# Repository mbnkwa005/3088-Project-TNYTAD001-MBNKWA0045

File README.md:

# EEE3088F Micro-Mouse Project

### Authors
- Tadiwa Tanyanyiwa
- Kwanele Mabanga

Welcome to the GitHub repository for our project!, which includes two key submodules: the Power submodule and the Sensing submodule.
This repository serves as a central hub for managing and sharing all the relevant files, including datasheets, schematics, and code associated with each submodule.

## Submodules

### Power Submodule
The Power submodule is responsible for supplying the necessary electrical power to all components of the project. 
It ensures that all components are properly powered under different operational conditions.

### Sensing Submodule
The Sensing submodule deals with acquiring data from the physical environment through sensors.

## Repository Contents

- **Datasheets** - Contains all the technical datasheets for components used in both submodules. This includes information on specifications, usage, and limitations of components such as sensors and power management chips.

- **Schematics/Documentation** - Provides detailed pdf schematics for the design and layout of the electrical circuits used in the project. This includes diagrams for both the Power and Sensing submodules as well as the BOM files for each submodule

- **KiCad** - This folder contains all the KiCad Gerber files and KiCad schematics for each subsection.
- **Software** - This folder contains the code used to test the functionalty of the sensing subsystem.
  
### What Hardware you will need
- An STM32L476 Microcontroller
- STM Discovry Board with a STM32F051 Microcontroller (For Testing)
- A micro USB cable to flash code into the STM32FO microcontroller.

### What Software you will need
- STM32CubeIDE 1.13.1 (or newer version) or VSCode with STM32 Extension
- KiCAD 7.0 (or newer version)

## Additional Resources

For more information on specific components or for help with the setup and operation of the submodules, please refer to the datasheets and schematics found in their respective directories within this repository.

## Acknowledgments
Thank you to the UCT Electrical Engineering Department for allowing us to do this cool project!

## Contact

For further inquiries or issues, please contact Tadiwa (tnytad001@myuct.ac.za) and Kwanele (mbnkwa005@myuct.ac.za).

Thank you for visiting our project repository!

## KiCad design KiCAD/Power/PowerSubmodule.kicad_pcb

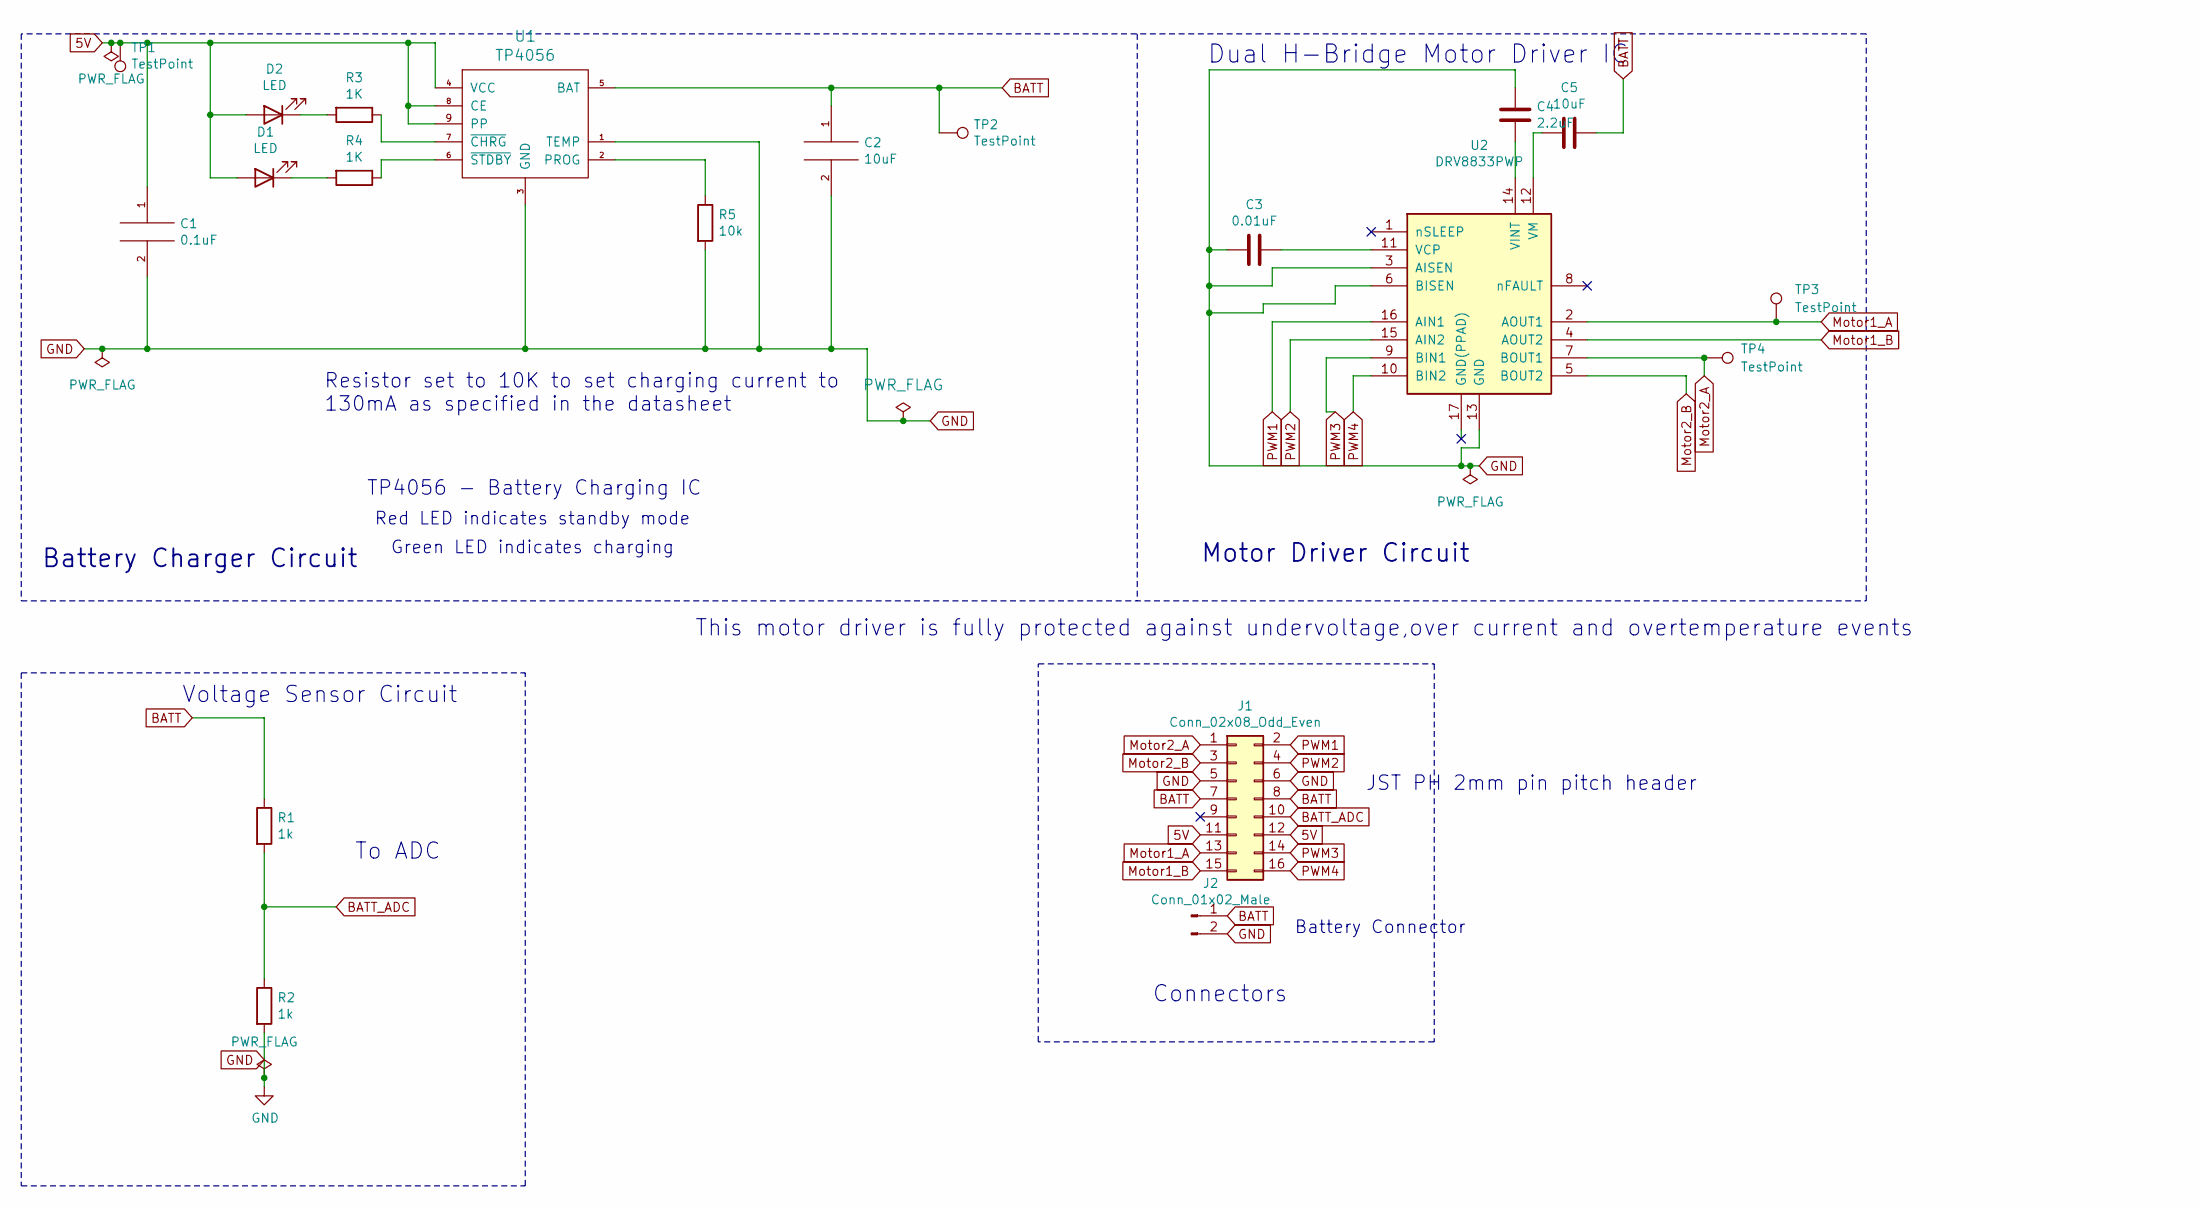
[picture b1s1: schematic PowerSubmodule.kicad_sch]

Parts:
C1: 0.1uF; C_0402_1005Metric
C2, C5: 10uF; C_0603_1608Metric
C3: 0.01uF; C_0402_1005Metric
C4: 2.2uF; C_0402_1005Metric
D1: LED; LED_0603_1608Metric
D2: LED; LED_0805_2012Metric
J1: Conn_02x08_Odd_Even; PinHeader_2x08_P2.54mm_Vertical
J2: Conn_01x02_Male; JST_JWPF_B02B-JWPF-SK-R_1x02_P2.00mm_Vertical
R1, R2: 1k; R_0402_1005Metric
R3, R4: 1K; R_0402_1005Metric
R5: 10k; R_0402_1005Metric
TP1: TestPoint; TestPoint_THTPad_D1.0mm_Drill0.5mm
TP2: TestPoint; TestPoint_THTPad_D1.5mm_Drill0.7mm
TP3, TP4: TestPoint
U1: TP4056; SOP127P600X175-9N
U2: DRV8833PWP; HTSSOP-16-1EP_4.4x5mm_P0.65mm_EP3.4x5mm_Mask2.46x2.31mm_The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

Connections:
5V: C1.1, D1.2 (A), D2.2 (A), J1.11, J1.12, TP1.1, U1.4 (VCC), U1.8 (CE), U1.9 (PP)
BATT: C2.1, C5.1, J1.7, J1.8, J2.1, R1.1, TP2.1, U1.5 (BAT)
BATT_ADC: J1.10, R1.2, R2.1
GND: C1.2, C2.2, C3.1, C4.1, J1.5, J1.6, J2.2, R2.2, R5.2, U1.1 (TEMP), U1.3 (GND), U2.3 (AISEN), U2.6 (BISEN), U2.13 (GND)
Motor1_A: J1.13, TP3.1, U2.2 (AOUT1)
Motor1_B: J1.15, U2.4 (AOUT2)
Motor2_A: J1.1, TP4.1, U2.7 (BOUT1)
Motor2_B: J1.3, U2.5 (BOUT2)
unnamed: D1.1 (K), R4.2
unnamed: D2.1 (K), R3.2
unnamed: R5.1, U1.2 (PROG)
unnamed: R3.1, U1.7 (~CHRG)
unnamed: R4.1, U1.6 (~STDBY)
unnamed: C3.2, U2.11 (VCP)
unnamed: C4.2, U2.14 (VINT)
unnamed: C5.2, U2.12 (VM)
PWM1: J1.2, U2.16 (AIN1)
PWM2: J1.4, U2.15 (AIN2)
PWM3: J1.14, U2.9 (BIN1)
PWM4: J1.16, U2.10 (BIN2)

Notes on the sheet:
TP4056 - Battery Charging IC
Voltage Sensor Circuit
Battery Charger Circuit
This motor driver is fully protected against undervoltage,over current and overtemperature events
Dual H-Bridge Motor Driver IC
Motor Driver Circuit
Resistor set to 10K to set charging current to 130mA as specified in the datasheet
Connectors
Battery Connector
To ADC
Red LED indicates standby mode
Green LED indicates charging
JST PH 2mm pin pitch header

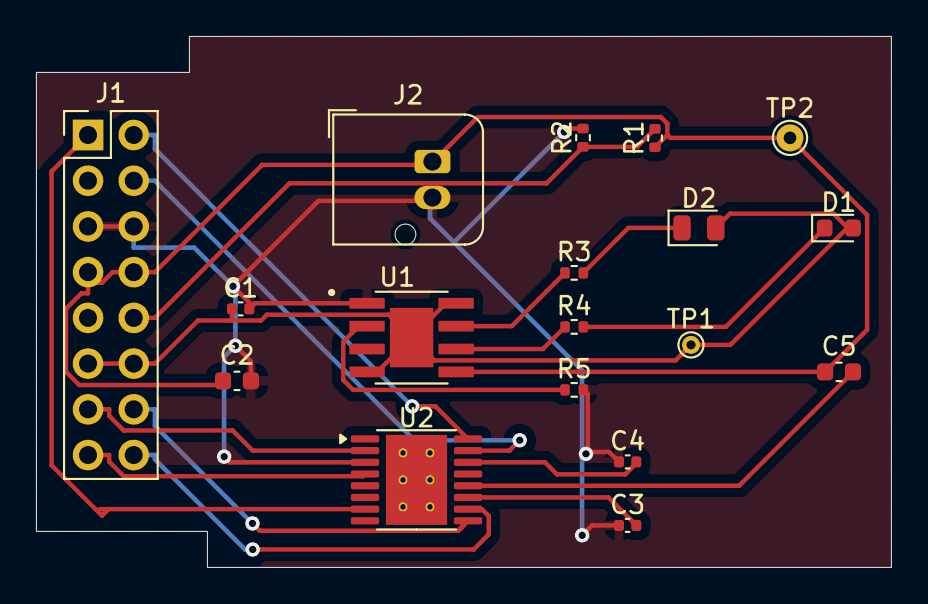
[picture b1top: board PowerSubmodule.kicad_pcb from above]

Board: 2 copper layers, 47.5 x 29.5 mm, 18 parts (0 on the bottom side), 20 nets.

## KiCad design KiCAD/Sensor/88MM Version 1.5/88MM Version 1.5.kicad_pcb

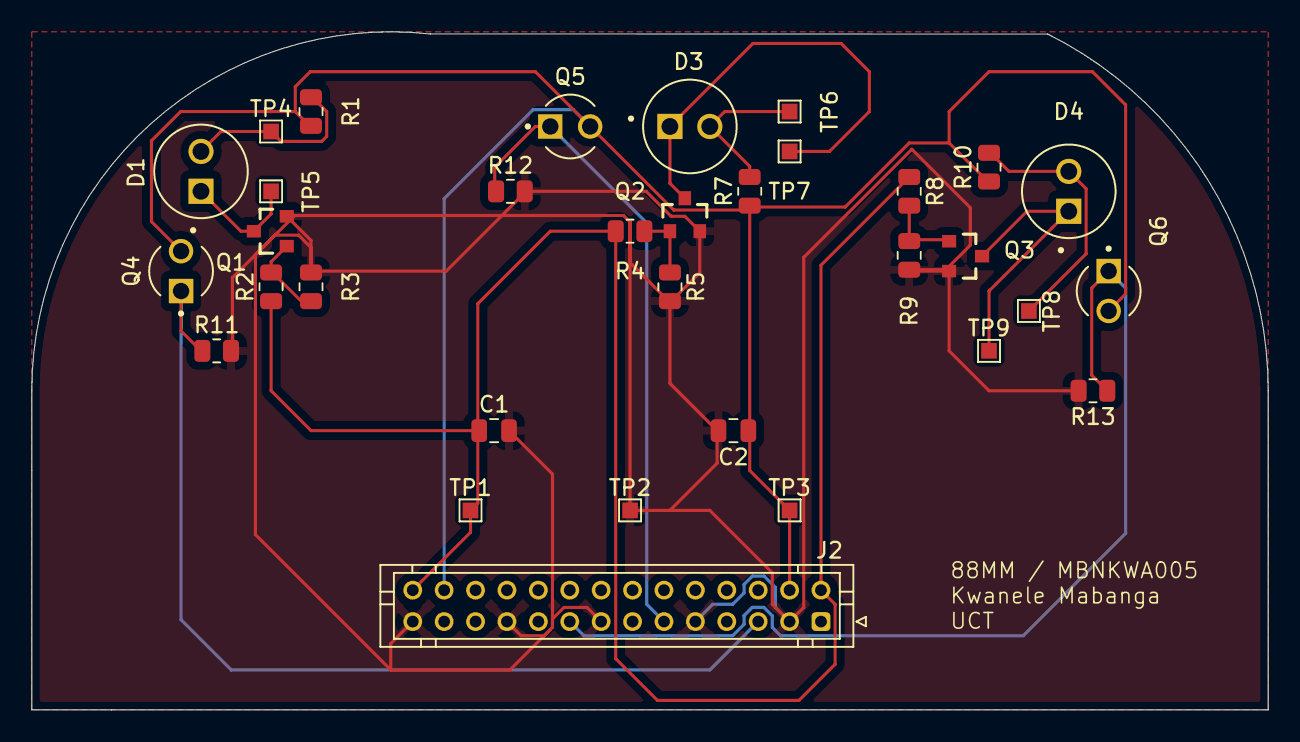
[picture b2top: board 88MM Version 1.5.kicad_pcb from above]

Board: 2 copper layers, 78.7 x 43.2 mm, 33 parts (0 on the bottom side), 15 nets.

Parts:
C1, C2: 10nF; C_0805_2012Metric
D1, D3, D4: TSAL6200; LEDRD254W55D595H900
J2: Conn_02x14_Odd_Even; JST_PHD_B28B-PHDSS_2x14_P2.00mm_Vertical
Q1, Q2, Q3: MMBT5551; SOT23-3
Q4, Q5, Q6: TEFT4300; XDCR_TEFT4300
R1, R7, R10: 220; R_0805_2012Metric
R2, R4, R8: 100; R_0805_2012Metric
R3, R5, R9, R11, R12, R13: 10k; R_0805_2012Metric
TP1, TP2, TP3, TP4, TP5, TP6, TP7, TP8, TP9: TestPoint; TestPoint_Pad_1.0x1.0mm

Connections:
+3V3: C1.1, J2.2, J2.28, R2.1, R4.1, R8.1, TP1.1
+BATT: C2.1, J2.4, J2.26, Q4.C, Q5.C, Q6.C, R1.1, R7.1, R10.1, TP3.1
/IR_LED_1A: D1.A, R1.2, TP4.1
/IR_LED_2A: D3.A, R7.2, TP6.1
/IR_LED_2C: D3.C, Q2.3, TP7.1
/IR_LED_3A: D4.A, R10.2, TP8.1
/IR_LED_3C: D4.C, Q3.3, TP9.1
/IR_LED_C: D1.C, Q1.3, TP5.1
/PA3: J2.5, Q4.E, R11.1
/PA5: J2.11, Q5.E, R12.1
/PA7: J2.17, Q6.E, R13.1
GND: C1.2, C2.2, J2.3, J2.9, J2.15, J2.21, J2.27, Q1.2, Q2.2, Q3.2, R3.2, R5.2, R9.2, R11.2, R12.2, R13.2, TP2.1
unnamed: Q1.1, R2.2, R3.1
unnamed: Q2.1, R4.2, R5.1
unnamed: Q3.1, R8.2, R9.1

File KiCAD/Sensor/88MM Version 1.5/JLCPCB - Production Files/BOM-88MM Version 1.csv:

Comment,Designator,Footprint,LCSC
TEFT4300,"Q4,Q5,Q6",XDCR_TEFT4300,C118301
MMBT5551,"Q1,Q2,Q3",SOT23-3,C2145
10k,"R11,R12,R13,R3,R5,R9",R_0805_2012Metric,C22775
220,"R1,R10,R7",R_0805_2012Metric,C22962
100,"R2,R4,R8",R_0805_2012Metric,C25804
TSAL6200,"D1,D3,D4",LEDRD254W55D595H900,C55528
10nF,"C1,C2",C_0805_2012Metric,C57112

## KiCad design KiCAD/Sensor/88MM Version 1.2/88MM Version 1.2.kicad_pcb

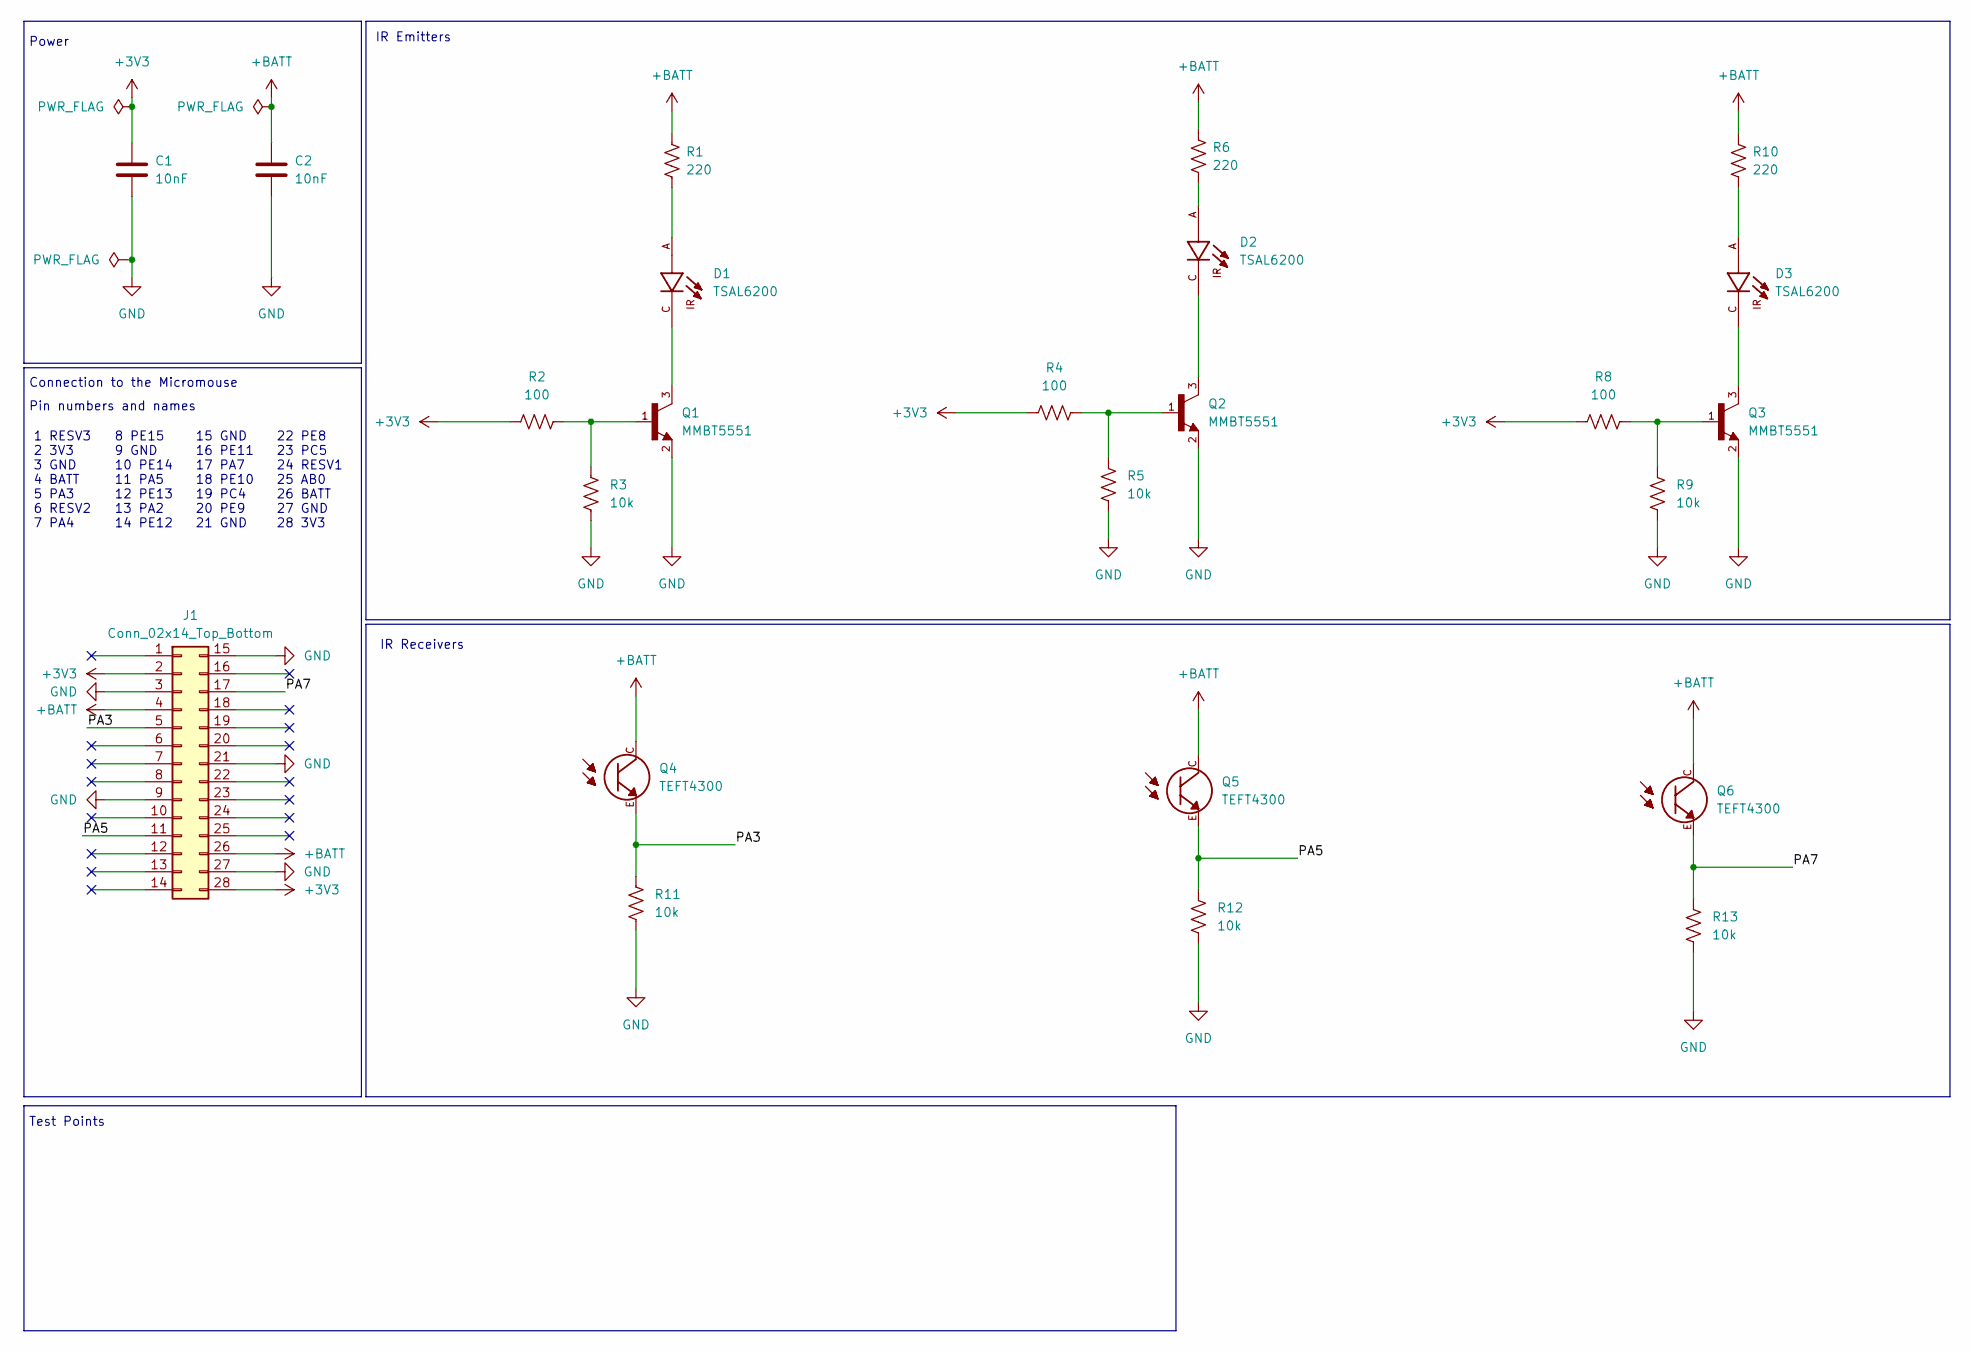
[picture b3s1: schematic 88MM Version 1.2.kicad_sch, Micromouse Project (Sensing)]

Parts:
C1, C2: 10nF; C_0805_2012Metric_Pad1.18x1.45mm_HandSolder
D1, D2, D3: TSAL6200; LEDRD254W55D595H900; PARTREV 2.4
J1: Conn_02x14_Top_Bottom; JST_PHD_B28B-PHDSS_2x14_P2.00mm_Vertical
Q1, Q2, Q3: MMBT5551; SOT23-3
Q4, Q5, Q6: TEFT4300; XDCR_TEFT4300; DigiKey_Part_Number 751-1041-ND
R1, R6, R10: 220; R_Axial_DIN0207_L6.3mm_D2.5mm_P2.54mm_Vertical
R2, R4, R8: 100; R_Axial_DIN0207_L6.3mm_D2.5mm_P2.54mm_Vertical
R3, R5, R9, R11, R12, R13: 10k; R_Axial_DIN0207_L6.3mm_D2.5mm_P2.54mm_Vertical

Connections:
+3V3: C1.1, J1.2, J1.28, R2.1, R4.1, R8.1
+BATT: C2.1, J1.4, J1.26, Q4.C, Q5.C, Q6.C, R1.1, R6.1, R10.1
/PA3: J1.5, Q4.E, R11.1
/PA5: J1.11, Q5.E, R12.1
/PA7: J1.17, Q6.E, R13.1
GND: C1.2, C2.2, J1.3, J1.9, J1.15, J1.21, J1.27, Q1.2, Q2.2, Q3.2, R3.2, R5.2, R9.2, R11.2, R12.2, R13.2
unnamed: D1.A, R1.2
unnamed: D1.C, Q1.3
unnamed: D2.A, R6.2
unnamed: D2.C, Q2.3
unnamed: D3.A, R10.2
unnamed: D3.C, Q3.3
unnamed: Q1.1, R2.2, R3.1
unnamed: Q2.1, R4.2, R5.1
unnamed: Q3.1, R8.2, R9.1

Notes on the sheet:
Connection to the Micromouse
Test Points
IR Receivers
Pin numbers and names
IR Emitters
22 PE8 23 PC5 24 RESV1 25 AB0 26 BATT 27 GND 28 3V3
1 RESV3 2 3V3 3 GND 4 BATT 5 PA3 6 RESV2 7 PA4
Power
15 GND 16 PE11 17 PA7 18 PE10 19 PC4 20 PE9 21 GND
8 PE15 9 GND 10 PE14 11 PA5 12 PE13 13 PA2 14 PE12

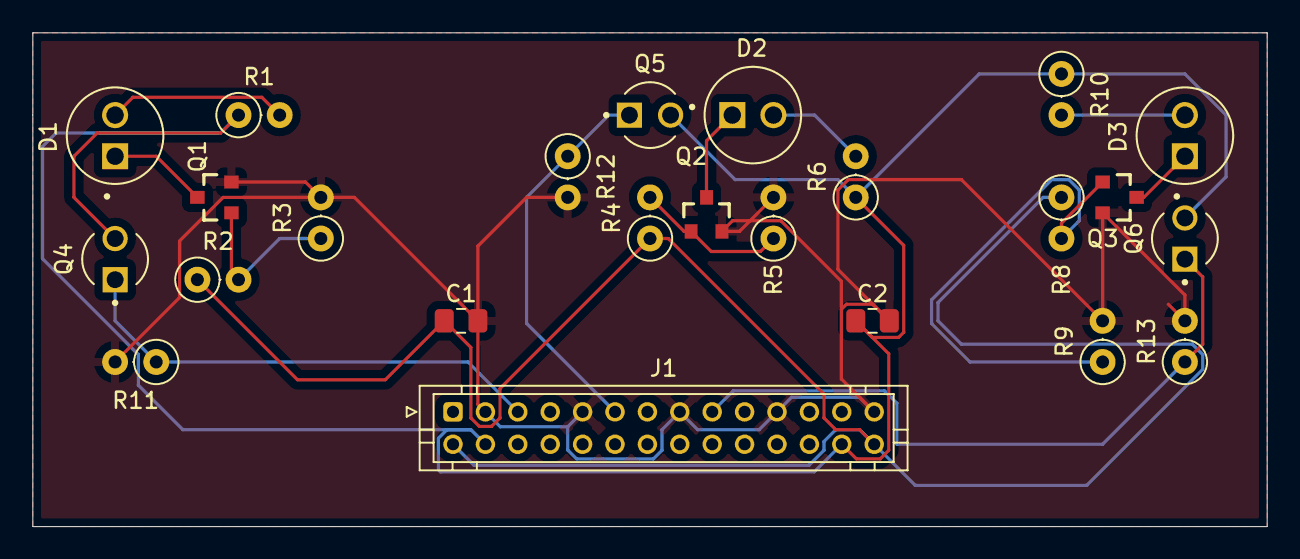
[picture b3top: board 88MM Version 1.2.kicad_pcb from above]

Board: 2 copper layers, 76.2 x 30.5 mm, 24 parts (0 on the bottom side), 15 nets.

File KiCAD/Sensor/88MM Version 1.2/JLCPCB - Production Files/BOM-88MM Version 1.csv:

Comment,Designator,Footprint,LCSC
MMBT5551,Q3,SOT23-3,
MMBT5551,Q2,SOT23-3,
MMBT5551,Q1,SOT23-3,
10k,R13,R_Axial_DIN0207_L6.3mm_D2.5mm_P2.54mm_Vertical,
10k,R12,R_Axial_DIN0207_L6.3mm_D2.5mm_P2.54mm_Vertical,
10k,R11,R_Axial_DIN0207_L6.3mm_D2.5mm_P2.54mm_Vertical,
220,R10,R_Axial_DIN0207_L6.3mm_D2.5mm_P2.54mm_Vertical,
10k,R9,R_Axial_DIN0207_L6.3mm_D2.5mm_P2.54mm_Vertical,
100,R8,R_Axial_DIN0207_L6.3mm_D2.5mm_P2.54mm_Vertical,
220,R6,R_Axial_DIN0207_L6.3mm_D2.5mm_P2.54mm_Vertical,
10k,R5,R_Axial_DIN0207_L6.3mm_D2.5mm_P2.54mm_Vertical,
100,R4,R_Axial_DIN0207_L6.3mm_D2.5mm_P2.54mm_Vertical,
10k,R3,R_Axial_DIN0207_L6.3mm_D2.5mm_P2.54mm_Vertical,
100,R2,R_Axial_DIN0207_L6.3mm_D2.5mm_P2.54mm_Vertical,
220,R1,R_Axial_DIN0207_L6.3mm_D2.5mm_P2.54mm_Vertical,
TEFT4300,Q6,XDCR_TEFT4300,
TEFT4300,Q5,XDCR_TEFT4300,
TEFT4300,Q4,XDCR_TEFT4300,
TSAL6200,D3,LEDRD254W55D595H900,
TSAL6200,D2,LEDRD254W55D595H900,
TSAL6200,D1,LEDRD254W55D595H900,
10nF,C2,C_0805_2012Metric_Pad1.18x1.45mm_HandSolder,
10nF,C1,C_0805_2012Metric_Pad1.18x1.45mm_HandSolder,

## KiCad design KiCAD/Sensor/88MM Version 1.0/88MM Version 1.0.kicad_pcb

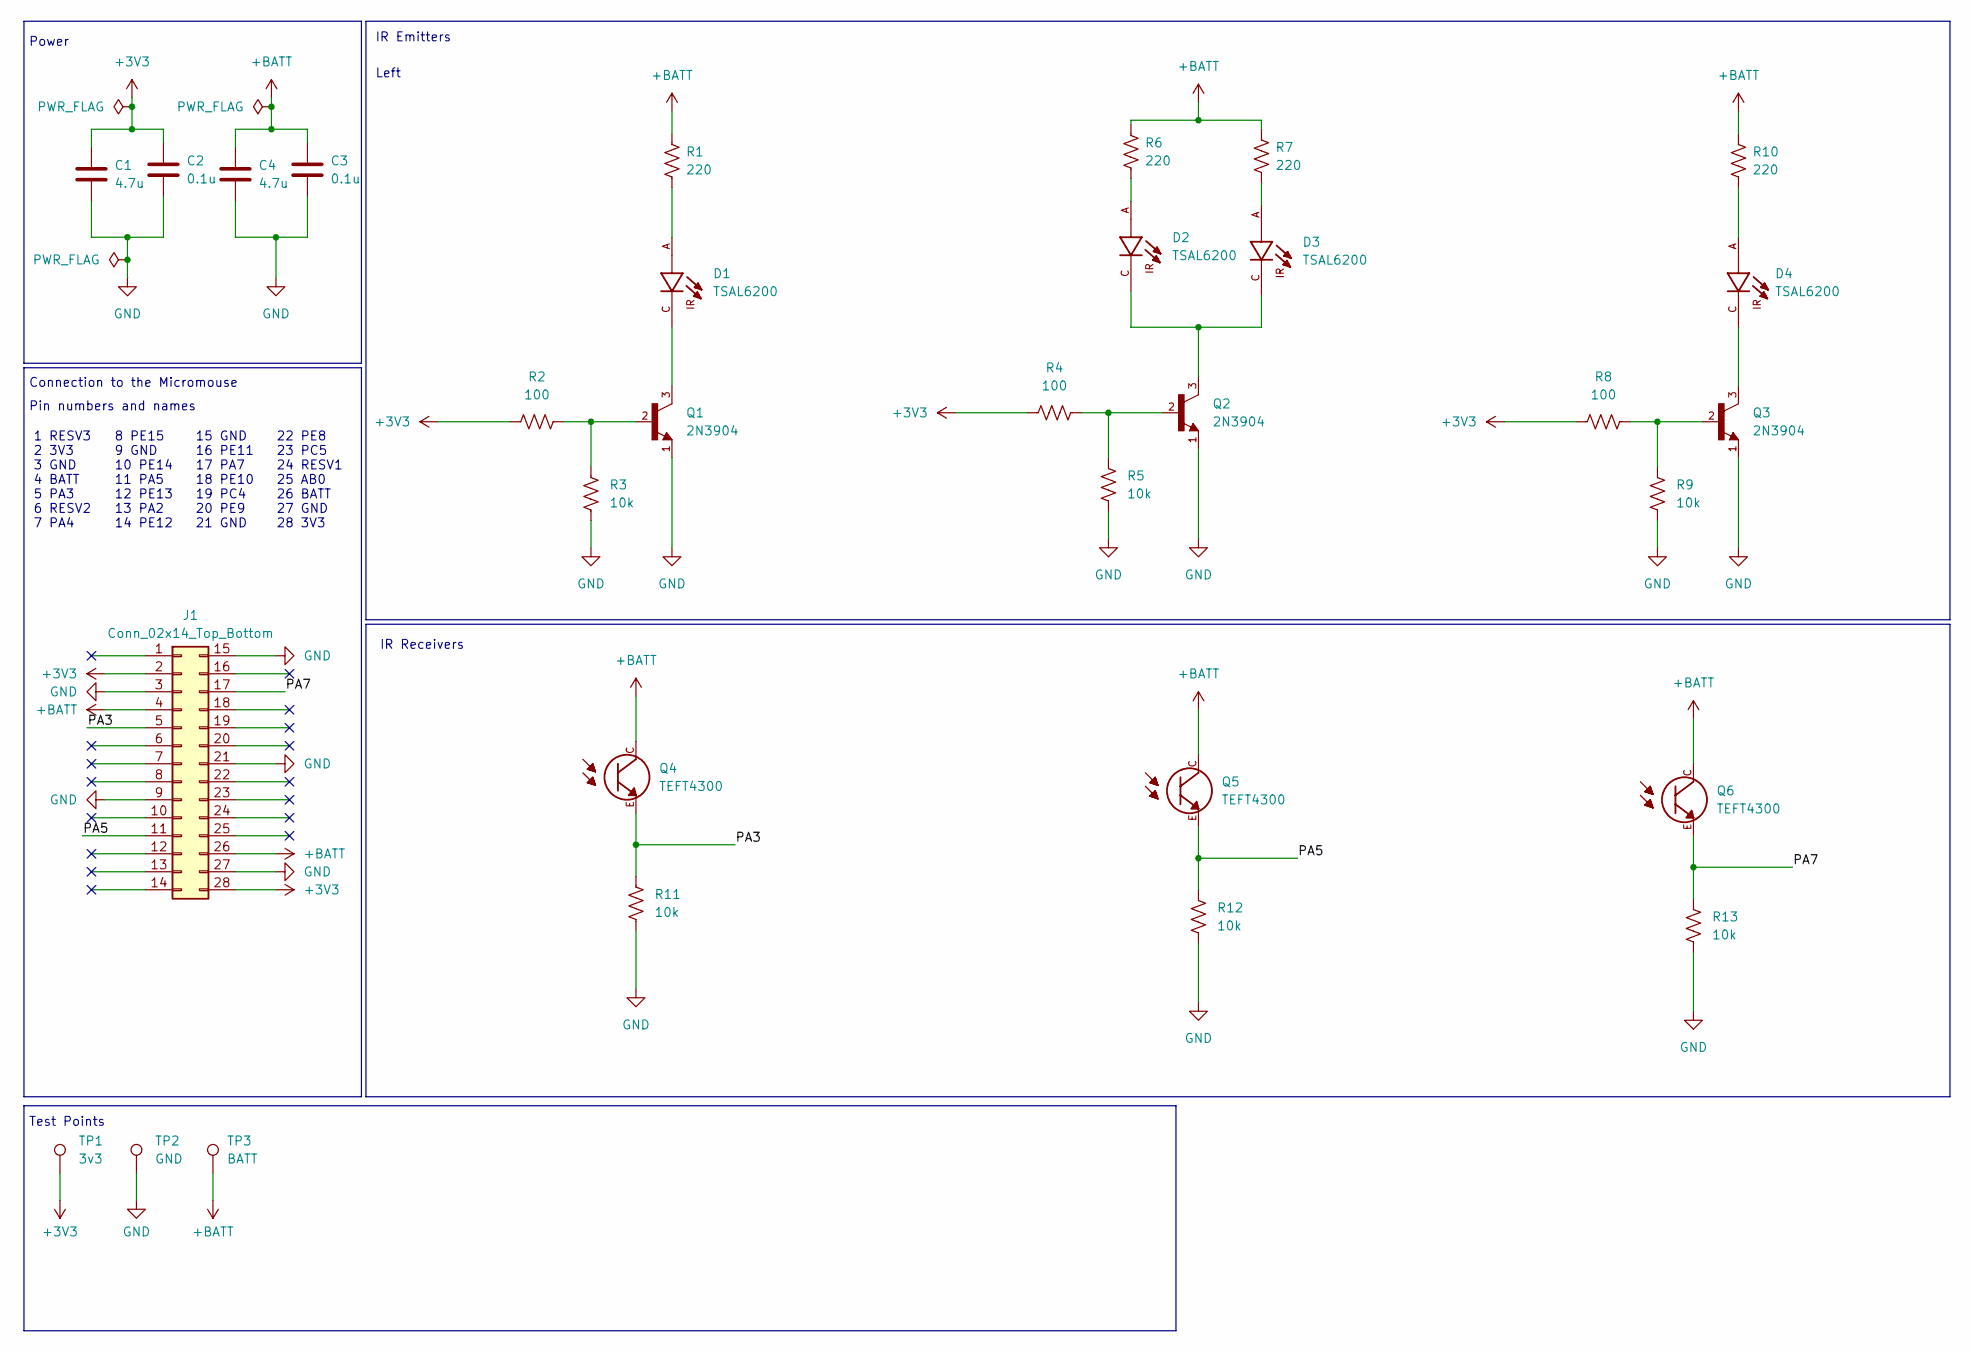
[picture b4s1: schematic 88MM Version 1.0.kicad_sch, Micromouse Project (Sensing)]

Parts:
C1, C4: 4.7u; CP_Radial_D5.0mm_P2.00mm
C2, C3: 0.1u; CP_Radial_D5.0mm_P2.00mm
D1, D2, D3, D4: TSAL6200; LEDRD254W55D595H900; PARTREV 2.4
J1: Conn_02x14_Top_Bottom; JST_PHD_B28B-PHDSS_2x14_P2.00mm_Vertical
Q1, Q2, Q3: 2N3904; TO92127P495H495-3; PARTREV February 2003
Q4, Q5, Q6: TEFT4300; XDCR_TEFT4300; DigiKey_Part_Number 751-1041-ND
R1, R6, R7, R10: 220; R_Axial_DIN0207_L6.3mm_D2.5mm_P2.54mm_Vertical
R2, R4, R8: 100; R_Axial_DIN0207_L6.3mm_D2.5mm_P2.54mm_Vertical
R3, R5, R9, R11, R12, R13: 10k; R_Axial_DIN0207_L6.3mm_D2.5mm_P2.54mm_Vertical
TP1: 3v3; TestPoint_Pad_D1.0mm
TP2: GND; TestPoint_Pad_D1.0mm
TP3: BATT; TestPoint_Pad_D1.0mm

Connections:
+3V3: C1.1, C2.1, J1.2, J1.28, R2.1, R4.1, R8.1, TP1.1
+BATT: C3.1, C4.1, J1.4, J1.26, Q4.C, Q5.C, Q6.C, R1.1, R6.1, R7.1, R10.1, TP3.1
/PA3: J1.5, Q4.E, R11.1
/PA5: J1.11, Q5.E, R12.1
/PA7: J1.17, Q6.E, R13.1
GND: C1.2, C2.2, C3.2, C4.2, J1.3, J1.9, J1.15, J1.21, J1.27, Q1.1, Q2.1, Q3.1, R3.2, R5.2, R9.2, R11.2, R12.2, R13.2, TP2.1
unnamed: D1.A, R1.2
unnamed: D1.C, Q1.3
unnamed: D2.A, R6.2
unnamed: D2.C, D3.C, Q2.3
unnamed: D3.A, R7.2
unnamed: D4.A, R10.2
unnamed: D4.C, Q3.3
unnamed: Q1.2, R2.2, R3.1
unnamed: Q2.2, R4.2, R5.1
unnamed: Q3.2, R8.2, R9.1

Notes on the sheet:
Connection to the Micromouse
Test Points
IR Receivers
Left
Pin numbers and names
IR Emitters
22 PE8 23 PC5 24 RESV1 25 AB0 26 BATT 27 GND 28 3V3
1 RESV3 2 3V3 3 GND 4 BATT 5 PA3 6 RESV2 7 PA4
Power
15 GND 16 PE11 17 PA7 18 PE10 19 PC4 20 PE9 21 GND
8 PE15 9 GND 10 PE14 11 PA5 12 PE13 13 PA2 14 PE12

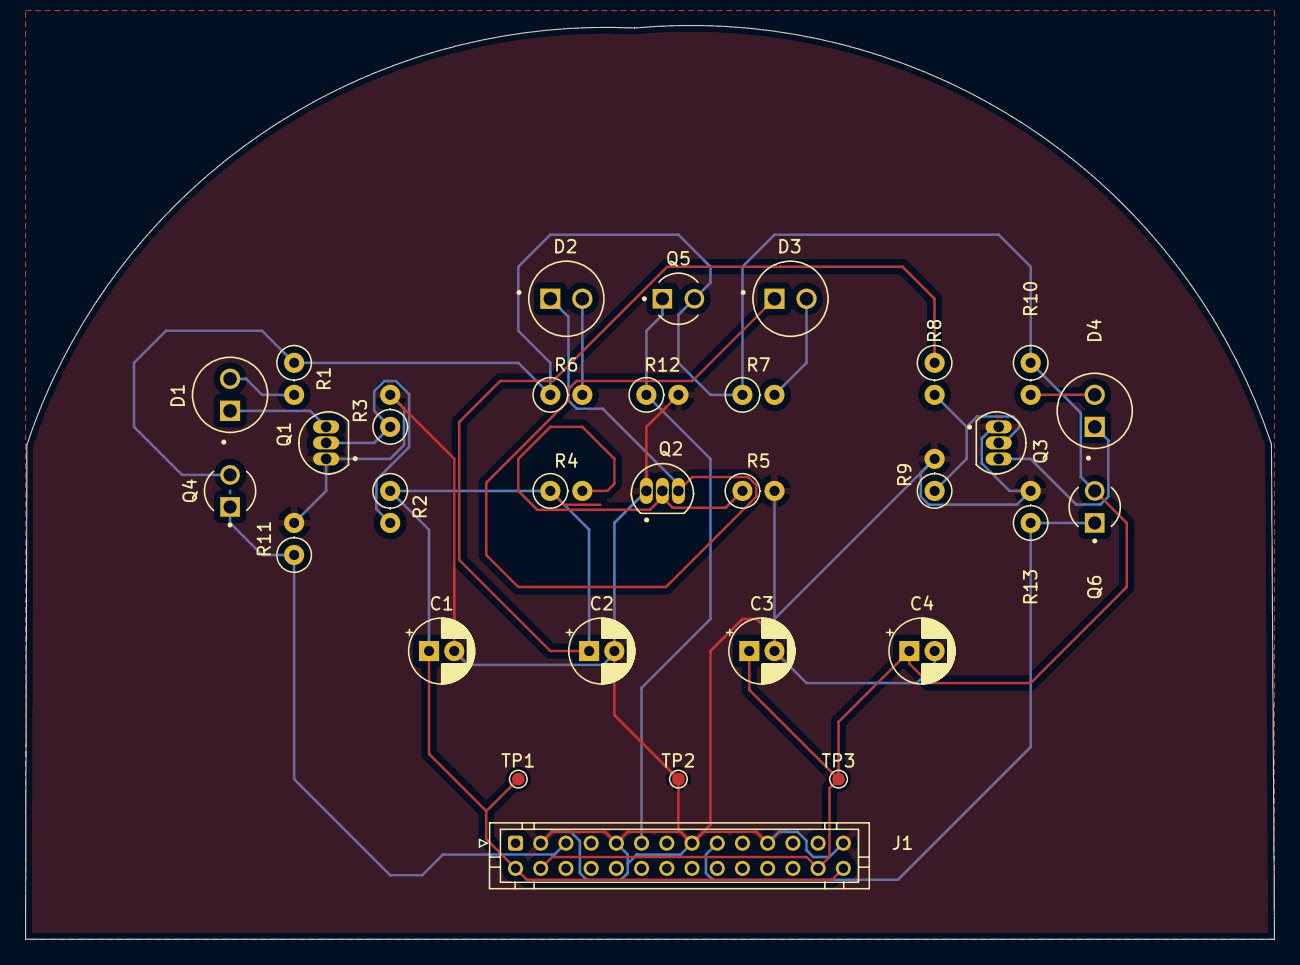
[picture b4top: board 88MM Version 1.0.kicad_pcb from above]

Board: 2 copper layers, 99.1 x 72.5 mm, 31 parts (0 on the bottom side), 16 nets.

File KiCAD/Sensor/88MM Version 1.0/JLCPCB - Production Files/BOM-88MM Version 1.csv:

Comment;Designator;Footprint;LCSC
TEFT4300;Q4,Q5,Q6;XDCR_TEFT4300;C118301
4.7u;C1,C4;CP_Radial_D5.00mm_P2.00mm;C19666
2N309;Q1,Q2,Q3;TO92127P495H495-3;C2150
100;R2,R4,R8;R_Axial_DIN0207_L6.3mm_D2.5mm_P2.54mm_Vertical;C22775
220;R1,R10,R6,R7;R_Axial_DIN0207_L6.3mm_D2.5mm_P2.54mm_Vertical;C22962
0,1u;C2,C3;CP_Radial_D5.0mm_P2.00mm;C24497
10k;R11,R12,R13,R3,R5,R9;R_Axial_DIN0207_L6.3mm_D2.5mm_P2.54mm_Vertical;C25804
TSAL6200;D1,D2,D3,D4;LEDRD254W55D595H900;C55528
;;;
